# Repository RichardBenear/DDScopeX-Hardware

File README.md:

# DDScope-Hardware
Hardware documentation for Direct Drive Scope

## Book: BUILD A DIRECT DRIVE TELESCOPE: A Comprehensive Guide
Book Available on Amazon [Here](https://a.co/d/0cUrQWGB)

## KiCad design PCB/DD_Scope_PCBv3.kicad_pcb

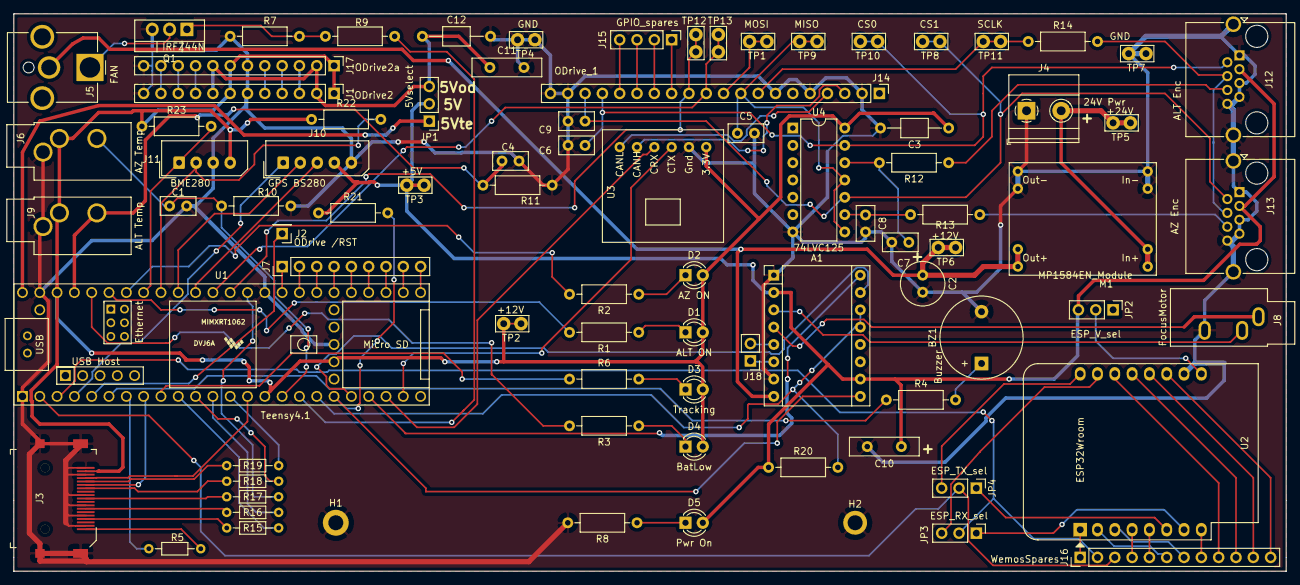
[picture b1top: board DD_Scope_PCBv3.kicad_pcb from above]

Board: 2 copper layers, 186.7 x 81.8 mm, 85 parts (0 on the bottom side), 103 nets.

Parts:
A1: A4988_Breakout; Pololu_Breakout-16_15.2x20.3mm
BZ1: Buzzer; Buzzer_12x9.5RM7.6
C1, C4: 680pf; C_Disc_D5.0mm_W2.5mm_P2.50mm
C2: 47uf; C_Radial_D6.3mm_H7.0mm_P2.50mm
C3, C12: 0.1uf; C_Axial_L3.8mm_D2.6mm_P10.00mm_Horizontal
C5, C7, C8: 100pf; C_Disc_D5.0mm_W2.5mm_P2.50mm
C6, C9: 68pf; C_Disc_D5.0mm_W2.5mm_P2.50mm
C10, C11: 2uf; C_Disc_D10.0mm_W2.5mm_P5.00mm
D1: ALT ON; LED_D3.0mm
D2: AZ ON; LED_D3.0mm
D3: Tracking; LED_D3.0mm
D4: BatLow; LED_D3.0mm
D5: Pwr On; LED_D3.0mm
H1: MountingHole_Pad; MountingHole_2.2mm_M2_DIN965_Pad
H2: MountingHole_Pad; MountingHole_2.2mm_M2_ISO7380_Pad
J1: ODrive2; PinHeader_1x12_P2.54mm_Vertical
J2: ODrive /RST; PinHeader_1x01_P2.54mm_Vertical
J3: Touchscreen; HDMI_A_Female_2000-1-2-41-00-BK
J4: 24V Pwr; TerminalBlock_Phoenix_MKDS-1,5-2-5.08_1x02_P5.08mm_Horizont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
J5: FAN; BarrelJack_CUI_PJ-063AH_Horizontal_CircularHoles
J6: AZ Temp; Jack_3.5mm_CUI_SJ1-3533NG_Horizontal_CircularHoles
J7: Spares; PinHeader_1x09_P2.54mm_Vertical
J8: FocusMotor; Jack_3.5mm_CUI_SJ1-3533NG_Horizontal
J9: ALT Temp; Jack_3.5mm_CUI_SJ1-3533NG_Horizontal_CircularHoles
J10: GPS BS280; Molex_SPOX_5267-05A_1x05_P2.50mm_Vertical
J11: BME280; Molex_SPOX_5267-04A_1x04_P2.50mm_Vertical
J12: ALT Enc; RJ45_Amphenol_RJHSE5380
J13: AZ Enc; RJ45_Amphenol_RJHSE5380
J14: ODrive_1; PinHeader_1x20_P2.54mm_Vertical
J15: GPIO_spares; PinHeader_1x04_P2.54mm_Vertical
J16: WemosSpares; PinHeader_1x12_P2.54mm_Vertical
J17: ODrive2a; PinHeader_1x12_P2.54mm_Vertical
J18: StepB; PinHeader_1x02_P2.54mm_Vertical
JP1: 5Vselect; PinHeader_1x03_P2.54mm_Vertical
JP2: ESP_V_sel; PinHeader_1x03_P2.54mm_Vertical
JP3: ESP_RX_sel; PinHeader_1x03_P2.54mm_Vertical
JP4: ESP_TX_sel; PinHeader_1x03_P2.54mm_Vertical
M1: MP1584EN_Module
Q1: IRFZ44N; TO-220-3_Vertical
R1, R2, R3, R6, R8: 220; R_Axial_DIN0207_L6.3mm_D2.5mm_P10.16mm_Horizontal
R4: 100; R_Axial_DIN0207_L6.3mm_D2.5mm_P10.16mm_Horizontal
R5: 22; R_Axial_DIN0204_L3.6mm_D1.6mm_P7.62mm_Horizontal
R7, R10, R11, R20, R21: 10K; R_Axial_DIN0207_L6.3mm_D2.5mm_P10.16mm_Horizontal
R9: 2.2K; R_Axial_DIN0207_L6.3mm_D2.5mm_P10.16mm_Horizontal
R12, R13: 50; R_Axial_DIN0207_L6.3mm_D2.5mm_P10.16mm_Horizontal
R14: 20; R_Axial_DIN0207_L6.3mm_D2.5mm_P10.16mm_Horizontal
R15, R16, R17, R18, R19: 47; R_Axial_DIN0204_L3.6mm_D1.6mm_P7.62mm_Horizontal
R22, R23: 4.7k; R_Axial_DIN0207_L6.3mm_D2.5mm_P10.16mm_Horizontal
TP1: MOSI; TestPoint_Bridge_Pitch2.54mm_Drill1.0mm
TP2, TP6: +12V; TestPoint_Bridge_Pitch2.54mm_Drill1.0mm
TP3: +5V; TestPoint_Bridge_Pitch2.54mm_Drill1.0mm
TP4, TP7: GND; TestPoint_Bridge_Pitch2.54mm_Drill1.0mm
TP5: +24V; TestPoint_Bridge_Pitch2.54mm_Drill1.0mm
TP8: CS1; TestPoint_Bridge_Pitch2.54mm_Drill1.0mm
TP9: MISO; TestPoint_Bridge_Pitch2.54mm_Drill1.0mm
TP10: CS0; TestPoint_Bridge_Pitch2.54mm_Drill1.0mm
TP11: SCLK; TestPoint_Bridge_Pitch2.54mm_Drill1.0mm
TP12: tTX3; TestPoint_Bridge_Pitch2.54mm_Drill1.0mm
TP13: tRX3; TestPoint_Bridge_Pitch2.54mm_Drill1.0mm
U1: Teensy4.1; Teensy41
U2: ESP32Wroom; WEMOS_D1_mini_light
U3: CAN230_board
U4: 74LVC125; DIP-14_W7.62mm

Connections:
5Vte: JP1.1, U1.48
+3V3: C3.1, D1.2, D2.2, D3.2, D4.2, J1.1, J1.7, J3.18, J6.T, J9.T, J11.4, J17.1, J17.7, R22.1, R23.1, TP2.1, U1.15, U1.46, U1.51, U3.1, U4.14
+5V: A1.2, A1.10, C10.1, D5.2, J10.4, J12.3, J13.3, JP1.2, JP2.3, R20.1, R21.1, TP3.1
+12V: A1.8, C2.1, J5.2, M1.7, M1.8, TP6.1
/1A: A1.4, J8.S
/2A: A1.3, J8.T
/5.0Vod: C11.1, C12.1, J1.2, J1.8, J17.2, J17.8, JP1.3
/5Vesp: JP2.2, U2.9
/24V: J4.2, M1.1, M1.2, TP5.1
/AZ_TEMP: C1.1, J6.R, R10.1, U1.16
/BUZZ_EN: R4.1, U1.6
/CS0: C6.1, J12.2, J14.17, TP10.1, U4.13
/CS1: C9.1, J13.2, J14.18, TP8.1, U4.10
/D: J5.1, Q1.2
/DIR: A1.16, U1.21
/Data0: J12.6, R12.1
/Data1: J13.6, R13.1
/FAN_EN: R9.1, U1.17
/G: Q1.1, R7.1, R9.2
/GPIO3: J14.13, J15.1
/GPIO4: J14.14, J15.2
/GPIO5: J14.15, J15.3
/GPIO6: J14.16, J15.4
/M0-A: J1.9, J17.9
/M0-B: J1.10, J17.10
/M0-Z: J1.11, J17.11
/M1-A: J1.3, J17.3
/M1-B: J1.4, J17.4
/M1-Z: J1.5, J17.5
/ODnRESET: J2.1, U1.5
/PPS: J10.1, U1.4
/RX3: J14.12, TP12.1, U1.36
/RX4: J10.2, U1.39
/SCL1: J11.1, R23.2, U1.41
/SCLK: J12.4, J13.4, R14.2
/SDA1: J11.2, R22.2, U1.40
/SLEEP: A1.13, A1.14, R20.2, U1.18
/SP33: J7.9, U1.25
/SP34: J7.8, U1.26
/SP35: J7.7, U1.27
/SP36: J7.6, U1.28
/SP37: J7.5, U1.29
/SP38: J7.4, U1.30
/SP39: J7.3, U1.31
/SP40: J7.2, U1.32
/SP41: J7.1, U1.33
/STEP: A1.15, U1.20
/TRACK_LED: R6.1, U1.9
/TX3: J14.11, TP13.1, U1.37
/TX4: J10.3, U1.38
/dDC-R: J3.13, R18.2
/dMISO: J3.16, U1.14
/dMOSI: J3.15, R19.2
/dSCLK: J3.10, R17.2
/dnCS: J3.7, R16.2
/dnIRQ: J3.14, U1.8
/dnReset: J3.1, R5.2
/nEN: A1.9, R21.2, U1.19
/oMISO: C5.1, J14.9, TP9.1, U4.8, U4.11
/oMOSI: J14.10, TP1.1
/oSCLK: J14.8, R14.1, TP11.1
/tDC-R: R18.1, U1.11
/tMOSI: R19.1, U1.13
/tdnCS: R16.1, U1.12
/tnCS: R15.1, U1.10
/tsnCS: J3.4, R15.2
CAN_H: J14.3, U3.5
CAN_L: J14.4, U3.6
CAN_RX3: U1.22, U3.4
CAN_TX3: U1.23, U3.3
GND: A1.1, A1.7, BZ1.2, C1.2, C2.2, C3.2, C4.2, C5.2, C6.2, C7.2, C8.2, C9.2, C10.2, C11.2, C12.2, H1.1, H2.1, J1.6, J1.12, J3.2, J3.5, J3.8, J3.11, J3.17, J3.19, J3.SH, J4.1, J6.S, J8.R, J9.S, J10.5, J11.3, J12.1, J12.5, J12.7, J12.8, J12.SH, J13.1, J13.5, J13.7, J13.8, J13.SH, J14.2, J14.5, J14.7, J14.19, J14.20, J17.6, J17.12, M1.3, M1.4, M1.5, M1.6, Q1.3, R7.2, R8.2, R10.2, R11.2, TP4.1, TP7.1, U1.1, U1.34, U1.47, U1.52, U2.10, U3.2, U4.7
unnamed: A1.5, J18.2
unnamed: A1.6, J18.1
unnamed: BZ1.1, R4.2
unnamed: C4.1, J9.R, R11.1, U1.45
unnamed: C7.1, R12.2, U4.12
unnamed: C8.1, R13.2, U4.9
unnamed: D1.1, R1.1
unnamed: D2.1, R2.1
unnamed: D3.1, R6.2
unnamed: D4.1, R3.1
unnamed: D5.1, R8.1
unnamed: J16.1, U2.1
unnamed: J16.4, U2.4
unnamed: J16.5, U2.5
unnamed: J16.6, U2.2
unnamed: J16.7, U2.3
unnamed: J16.8, U2.8
unnamed: J16.9, U2.14
unnamed: J16.10, U2.13
unnamed: J16.11, U2.12
unnamed: J16.12, U2.11
unnamed: R1.2, U1.43
unnamed: R2.2, U1.42
unnamed: R3.2, U1.44
unnamed: R5.1, U1.7
RX1_t: J16.3, JP4.2, U1.2
RX_wPri: JP3.3, U2.15
RX_wSec: JP3.1, U2.7
TX1_t: J16.2, JP3.2, U1.3
TX_wPri: JP4.3, U2.16
TX_wSec: JP4.1, U2.6
tSCLK: R17.1, U1.35

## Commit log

2022-08-24 Initial
2022-08-31 Rename DD_Scope_PCB-rescue.lib to PCB/DD_Scope_PCB-rescue.lib
2023-02-22 Version3
2023-02-22 corrected GPIO pin number for CS0
2026-02-13 Corrected errors ODrive configuration settings and procedures
2026-02-13 Enhance ODrive setup instructions for motors
    Added detailed ODrive motor configuration settings and calibration procedures for both altitude and azimuth motors, including anticogging setup and startup procedures.
2026-02-21 updated with corrections -compatible with KiCad7
2026-02-21 Delete DDScope_TopLevel.pdf
    newer version in PCB folder
2026-02-23 Add book details and image to README
    Added book information and image to README.
